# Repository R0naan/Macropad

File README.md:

# Ronan's First Macropad

### Inspiration

I Wanted to Do a simple project that would teach me the basics of pcb design and KiCAD. I also wanted a macropad to help me improve my designing workflow
 
### Challenges

This was my first time using KiCad or any PCB software. I also was unfamiliar with autodesk fusion as I mainly use blender. It still fells a little complicated, but is getting easier as I work more

### Specifications

BOM: 
- 10x Cherry MX Switches
- 1x XIAO RP2040
- 10x Blank DSA Keycaps
- 4x M3x16 Bolt
- 4x M3 Heatset

Schematic            |  PCB         |   Case
:-------------------------:|:-------------------------:|:-------------------------:|
    |    |

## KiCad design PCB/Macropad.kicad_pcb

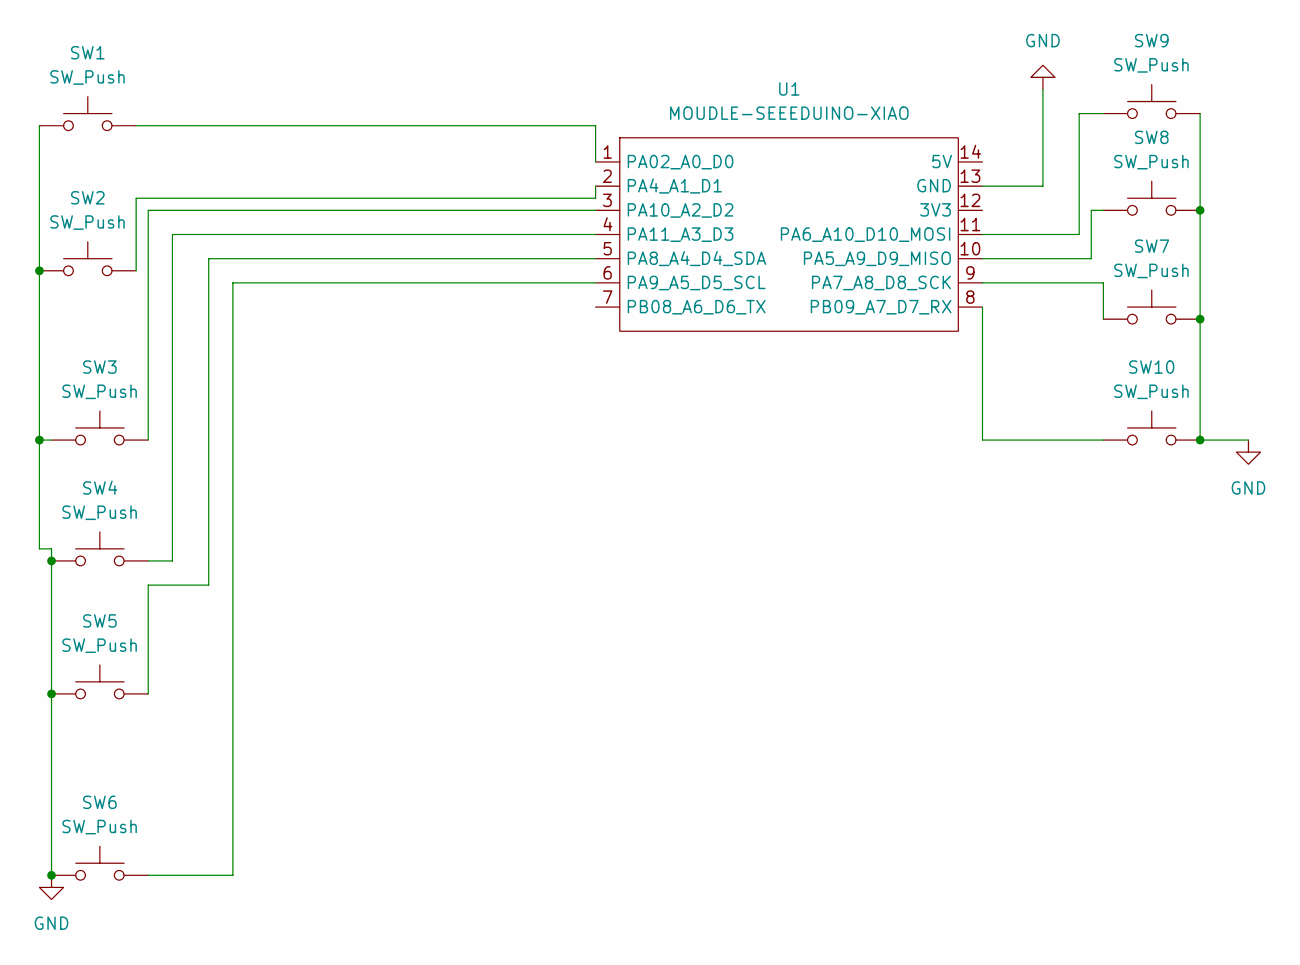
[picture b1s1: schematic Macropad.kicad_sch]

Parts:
SW1, SW2, SW3, SW4, SW5, SW6, SW7, SW8, SW9, SW10: SW_Push; SW_Cherry_MX_1.00u_PCB
U1: MOUDLE-SEEEDUINO-XIAO; XIAO-Generic-Hybrid-14P-2.54-21X17.8MM

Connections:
GND: SW1.1, SW2.1, SW3.1, SW4.1, SW5.1, SW6.1, SW7.2, SW8.2, SW9.2, SW10.2, U1.13 (GND)
unnamed: SW1.2, U1.1 (PA02_A0_D0)
unnamed: SW2.2, U1.2 (PA4_A1_D1)
unnamed: SW8.1, U1.10 (PA5_A9_D9_MISO)
unnamed: SW9.1, U1.11 (PA6_A10_D10_MOSI)
unnamed: SW7.1, U1.9 (PA7_A8_D8_SCK)
unnamed: SW5.2, U1.5 (PA8_A4_D4_SDA)
unnamed: SW6.2, U1.6 (PA9_A5_D5_SCL)
unnamed: SW3.2, U1.3 (PA10_A2_D2)
unnamed: SW4.2, U1.4 (PA11_A3_D3)
unnamed: SW10.1, U1.8 (PB09_A7_D7_RX)

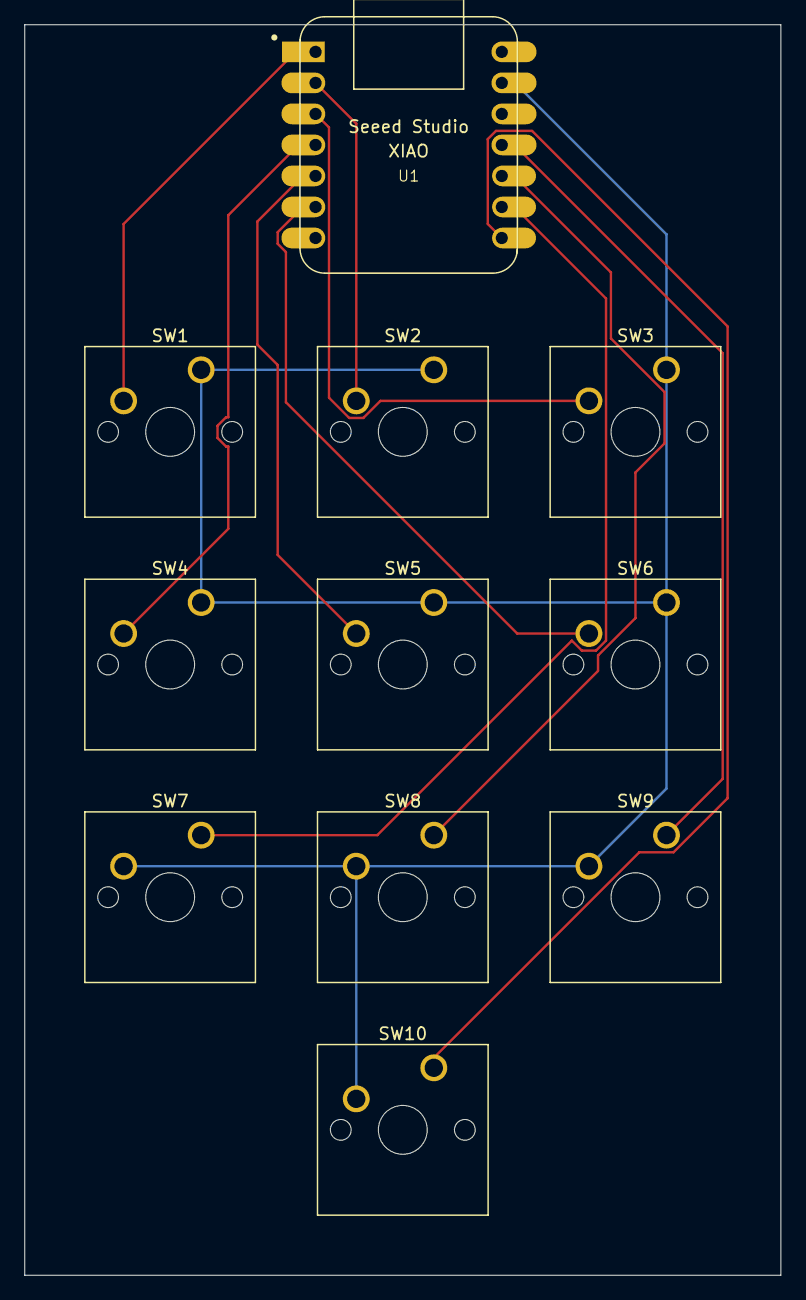
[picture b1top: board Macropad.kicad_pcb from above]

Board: 2 copper layers, 61.9 x 102.4 mm, 11 parts (0 on the bottom side), 11 nets.

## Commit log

2026-03-08 init commit
